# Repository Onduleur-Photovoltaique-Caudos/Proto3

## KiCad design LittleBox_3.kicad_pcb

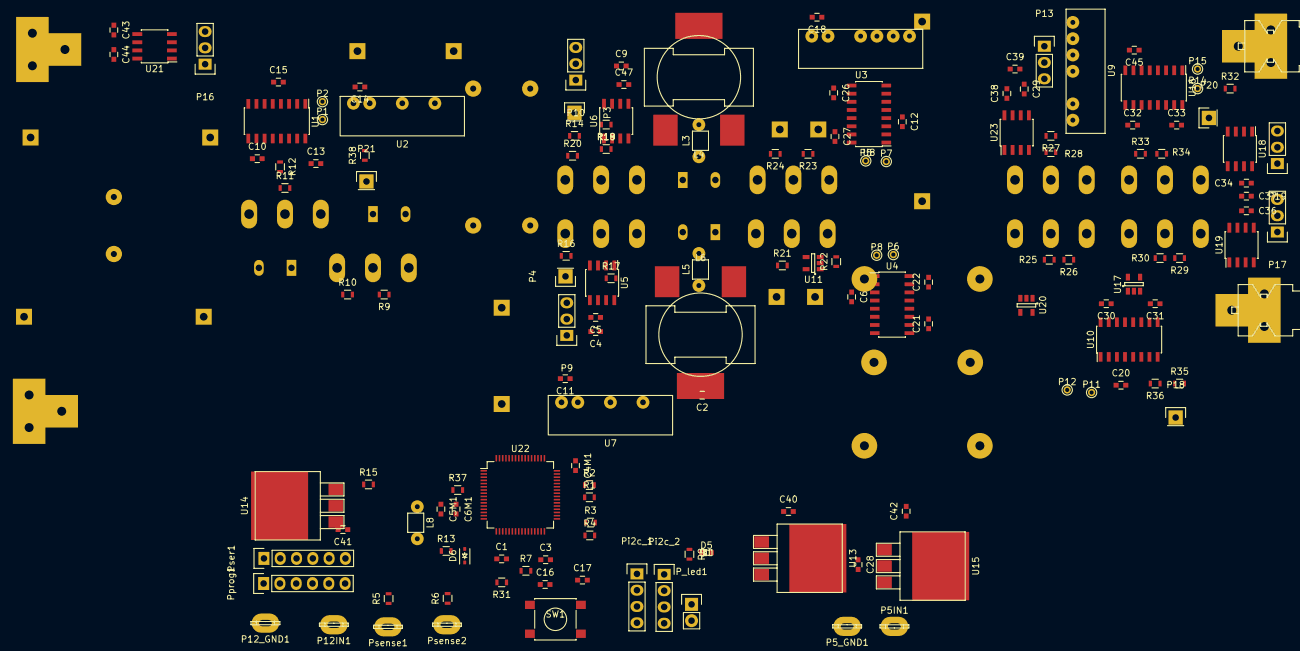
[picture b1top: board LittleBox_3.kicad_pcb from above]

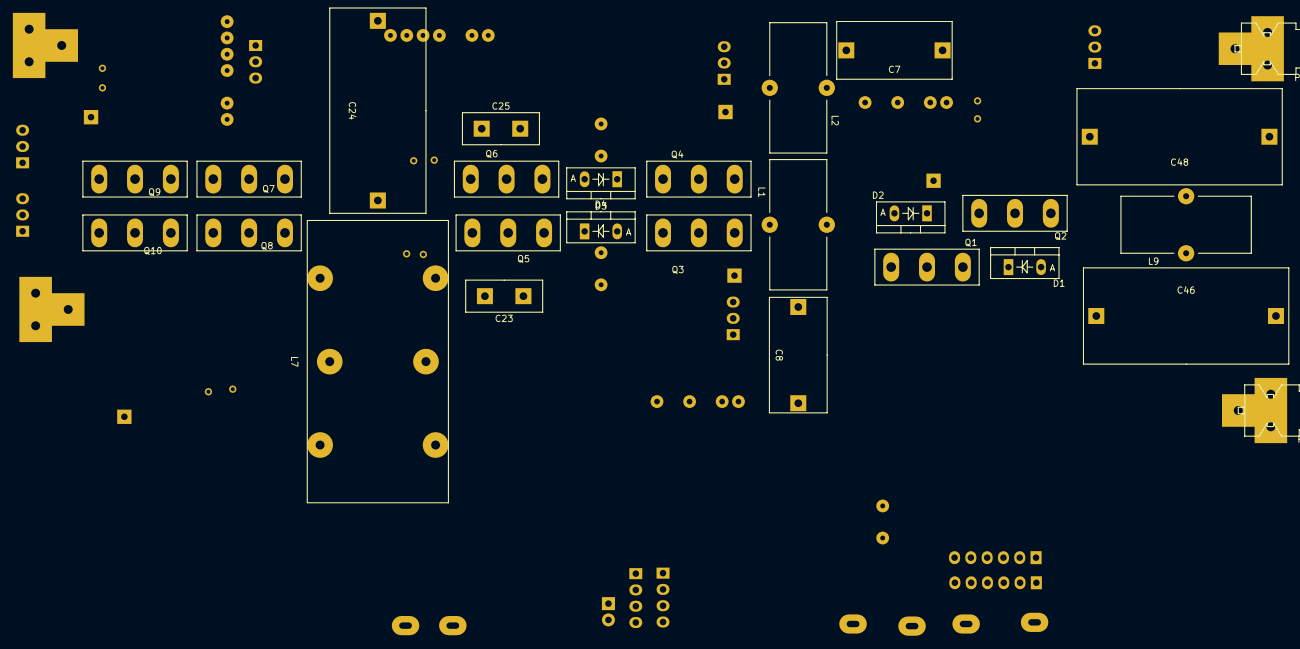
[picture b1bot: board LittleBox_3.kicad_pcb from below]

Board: 6 copper layers, 171 parts (27 on the bottom side), 109 nets, no tracks yet.

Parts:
C1, C2, C3, C4M1, C6, C12, C15, C17, C20, C34, C36, C37, C38, C39, C43, C44, C45: 100n; C_0603
C4, C5, C9, C47: 0.1u; C_0603
C5M1: 10n; C_0603
C6M1, C16, C28, C40, C41, C42: 1u; C_0603
C7, C8: 0.5u 250V; C_Rect_L18_W8_P15
C10, C11, C13, C14, C18, C21, C22, C26, C27, C29, C30, C31, C32, C33: 4.7u; C_0603
C23, C25: 1n 1000V; C_Rect_L12_W5_P6
C24, C46, C48: 2.2uF 630V; C_Rect_W15_L32_P27.5
D1, D2, D3, D4: C3D06060A; Diode_TO-220_Vertical
D5: LED; LED-0603
D6: SD1206S040S0R5; SOD-323
L1, L2: 470uH; 2100HT-471-V-RC
L3, L5: Bead; BEAD-5
L4, L6: 1uH; SER20xx-xxxL
L7: 1.2m; TOROID_15_44_22
L8: 2u; BEAD-5
L9: 330uH; 2100HT-471-V-RC
P1, P2, P5, P6, P7, P8, P11, P12, P14, P15: CONN_01X01; PINTST
P3, P4, P20: CONN_01X01; Socket_Strip_Straight_1x01
P5IN1, P5_GND1, P12IN1, P12_GND1: CONN_1; FASTON_110-1
P9, P10, P13, P16, P17, P19: CONN_01X03; Pin_Header_Straight_1x03
P18, P21: CONN_01X01; Pin_Header_Straight_1x01
P400IN+1, P400IN-1: CONN_1; FASTON250_Slanted30-1
POUT1, POUT2: CONN_1; FASTON250_Slanted30-1
P_led1: CONN_2; Pin_Header_Straight_1x02
Pi2c_1, Pi2c_2: CONN_4; Pin_Header_Straight_1x04
Pprog1: CONN_6; Pin_Header_Straight_1x06
Psense1, Psense2: CONN_1; FASTON_110-1
Pser1: CONN_6; Pin_Header_Straight_1x06
Q1, Q2, Q3, Q4, Q5, Q6: C3M0065090D; TO-247_Vertical_Neutral123
Q7, Q8, Q9, Q10: IPW6045CP; TO-247_Vertical_Neutral123
R1, R2, R3, R4: 0; R_0603
R5, R6, R7: 10k; R_0603
R8: 510; R_0603
R9, R11, R18, R19, R21, R23, R25, R28, R30, R34: 1k; R_0603
R10, R12, R17, R20, R22, R24, R26, R27, R29, R33: 1; R_0603
R13, R15, R31, R36, R37: 22K; R_0603
R14, R16, R32, R35, R38: 4.7M; R_0603
SW1: SW_PUSH; SW_SPST_PTS645
U1, U4, U8, U10, U16: ADUM3223; SOIC-16_3.9x9.9mm_Pitch1.27mm
U2, U7: B1212LS-1W
U3, U9: DY12D1212-2W
U5, U6, U18, U19, U21, U23: ACS712; SOIC-8_3.9x4.9mm_Pitch1.27mm
U11, U17, U20: IR25750; SOT-23-5
U13, U14: AZ1117-3.3; DPAK-3
U15: 7805; DPAK-3
U22: STM32F334R8T6; LQFP-64_10x10mm_Pitch0.5mm

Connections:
/B1: C23.1, C25.2, C26.1, L4.2, L6.1, L7.1, Q5.2, Q6.3, R23.1, U3.4, U8.9, U11.5
/H1_HON: P14.1, U16.2, U22.34
/H1_LON: P12.1, U10.1, U22.8
/H2_HON: P15.1, U16.1, U22.9
/H2_LON: P11.1, U10.2, U22.45
/M_I175: P10.2, R3.2, U6.7
/M_I225: P9.2, R1.2, U5.7
/M_IH1: U20.1, U22.24
/M_IH2: U17.1, U22.25
/M_IHFL: U11.1, U22.10
/M_IOUT1: P13.2, P19.2, R2.2, U18.7, U23.7
/M_IOUT2: P17.2, R4.2, U19.7
/M_VIN: P21.1, R37.1, R38.1
/ON225: P1.1, U1.2, U22.39
/PA1: P3.1, R13.2, R14.1, U22.15
/PA2: Pser1.3, U22.16
/PA3: Pser1.2, U22.17
/PA5: R8.1, U22.21
/PA6: P4.1, R15.2, R16.1, U22.22
/PA8: P7.1, U8.1, U22.41
/PA9: P8.1, U4.1, U22.42
/PA10: P6.1, U4.2, U22.43
/PA11: P5.1, U8.2, U22.44
/PA13: Pprog1.4, U22.46
/PA14: Pprog1.2, U22.49
/PB0: P20.1, R31.1, R32.1, U22.26
/PB1: P18.1, R35.2, R36.1, U22.27
/PB2: P16.2, U21.7, U22.28
/PB3: Pprog1.6, U22.55
/PB8: Pi2c_1.1, Pi2c_2.1, U22.61
/PB9: Pi2c_1.2, Pi2c_2.2, U22.62
/PB12: P2.1, U1.1, U22.33
/PB14: R3.1, R4.1, U22.35
/PB15: R1.1, R2.1, U22.36
/PC10: Pser1.5, U22.51
/inverter_microcontroller/BOO0: R7.1, U22.60
/inverter_microcontroller/NRST: C17.1, Pprog1.5, SW1.1, U22.7
/inverter_microcontroller/PD2: R5.1, U22.54
/inverter_microcontroller/VBAT: C16.1, U22.1
/inverter_microcontroller/VDD: C1.2, C2.2, C3.2, C4M1.1, D6.1, Pprog1.1, U22.19, U22.32, U22.48, U22.64
/inverter_microcontroller/VSS: C1.1, C2.1, C3.1, C4M1.2, Pprog1.3, U22.18, U22.31, U22.47, U22.63
DIS: U1.5, U4.5, U8.5, U10.5, U16.5, U22.6
GND_12: C11.1, C14.1, C18.1, C29.1, U2.2, U3.2, U7.2, U9.2
GND_A: C4.2, C5.2, C5M1.1, C6M1.1, C9.2, C34.1, C36.2, C37.2, C38.2, C39.2, C40.1, C43.1, C44.1, C47.2, P9.3, P10.3, P13.3, P16.3, P17.3, P19.3, R13.1, R15.1, R31.2, R36.2, R37.2, U5.5, U6.5, U13.1, U18.5, U19.5, U21.5, U22.12, U23.5
GND_P: C6.2, C7.2, C8.2, C10.1, C12.1, C15.2, C16.2, C17.2, C20.2, C22.1, C23.2, C24.2, C28.1, C30.1, C31.1, C41.1, C42.1, C46.1, C48.1, D2.1, D5.2, P5_GND1.1, P12_GND1.1, P400IN-1.1, P_led1.1, Pi2c_1.4, Pi2c_2.4, Pser1.4, Q1.3, Q5.3, Q8.3, Q10.3, R6.2, R7.2, R9.2, R21.1, R25.1, R30.1, SW1.2, U1.4, U1.9, U4.4, U4.14, U8.4, U10.4, U10.9, U10.14, U11.4, U14.1, U15.1, U17.4, U20.4
unnamed: C5.1, U5.6
unnamed: C5M1.2, C6M1.2, D6.2, L8.2, U22.13
unnamed: C7.1, L1.2, R16.2, U5.1, U5.2
unnamed: C8.1, L2.1, R14.2, U6.1, U6.2
unnamed: C13.1, D2.2, L2.2, Q2.3, R11.2, U1.14, U2.6
unnamed: C13.2, U1.16, U2.4
unnamed: C21.1, D3.2, Q3.3, R18.1, U4.9, U7.4
unnamed: C21.2, U4.11, U7.6
unnamed: C24.1, L7.2, U23.1, U23.2
unnamed: C26.2, U3.5, U8.11
unnamed: C27.2, U8.16
unnamed: C32.1, Q7.3, Q8.2, R28.1, U9.4, U16.9, U19.1, U19.2, U20.5
unnamed: C32.2, U9.5, U16.11
unnamed: C33.1, Q9.3, Q10.2, R34.1, U9.6, U16.14, U17.5, U18.3, U18.4
unnamed: C34.2, U18.6
unnamed: C36.1, U19.6
unnamed: C38.1, U23.6
unnamed: C43.2, U21.6
unnamed: C45.1, U16.4
unnamed: C47.1, U6.6
unnamed: C48.2, L9.1, U21.1, U21.2
unnamed: D1.1, L1.1, Q1.2
unnamed: D3.1, L5.1
unnamed: D4.1, Q4.2
unnamed: D4.2, L3.1
unnamed: D5.1, P_led1.2, R8.2
unnamed: L3.2, L4.1
unnamed: L5.2, L6.2
unnamed: P400IN+1.1, U21.3, U21.4
unnamed: POUT1.1, R32.2, U18.1, U18.2
unnamed: POUT2.1, R35.1, U19.3, U19.4
unnamed: Psense1.1, R5.2
unnamed: Psense2.1, R6.1
unnamed: Q1.1, R9.1, R10.2
unnamed: Q2.1, R11.1, R12.2
unnamed: Q3.1, R17.2, R18.2
unnamed: Q4.1, R19.1, R20.1
unnamed: Q5.1, R21.2, R22.2, U11.3
unnamed: Q6.1, R23.2, R24.2
unnamed: Q7.1, R27.2, R28.2
unnamed: Q7.2, Q9.2, U23.3, U23.4
unnamed: Q8.1, R25.2, R26.2, U20.3
unnamed: Q9.1, R33.2, R34.2
unnamed: Q10.1, R29.2, R30.2, U17.3
unnamed: R10.1, U1.10
unnamed: R12.1, U1.15
unnamed: R17.1, U4.10
unnamed: R20.2, U8.15
unnamed: R22.1, U4.15
unnamed: R24.1, U8.10
unnamed: R26.1, U10.15
unnamed: R27.1, U16.10
unnamed: R29.1, U10.10
unnamed: R33.1, U16.15
unnamed: U9.7, U16.16
V175: C27.1, Q4.3, R19.2, U3.6, U6.3, U6.4, U8.14
V225: Q3.2, U5.3, U5.4
V400+: C25.1, C46.2, D1.2, L9.2, Q2.2, Q6.2, R38.2
VCC3_A: C4.1, C9.1, C37.1, C39.1, C44.2, P9.1, P10.1, P13.1, P16.1, P17.1, P19.1, U5.8, U6.8, U18.8, U19.8, U21.8, U23.8
VCC5: C42.2, U13.3, U14.3, U15.2
VCC5_IN: C28.2, P5IN1.1, U15.3
VCC12: C10.2, C11.2, C14.2, C18.2, C22.2, C29.2, C30.2, C31.2, P12IN1.1, U1.11, U2.1, U3.1, U4.16, U7.1, U9.1, U10.11, U10.16
VDD3_A: C40.2, L8.1, U13.2
VDD3_D: C6.1, C12.2, C15.1, C20.1, C41.2, C45.2, Pi2c_1.3, Pi2c_2.3, Pser1.1, U1.3, U1.8, U4.3, U4.8, U8.3, U8.8, U10.3, U10.8, U14.2, U16.3, U16.8

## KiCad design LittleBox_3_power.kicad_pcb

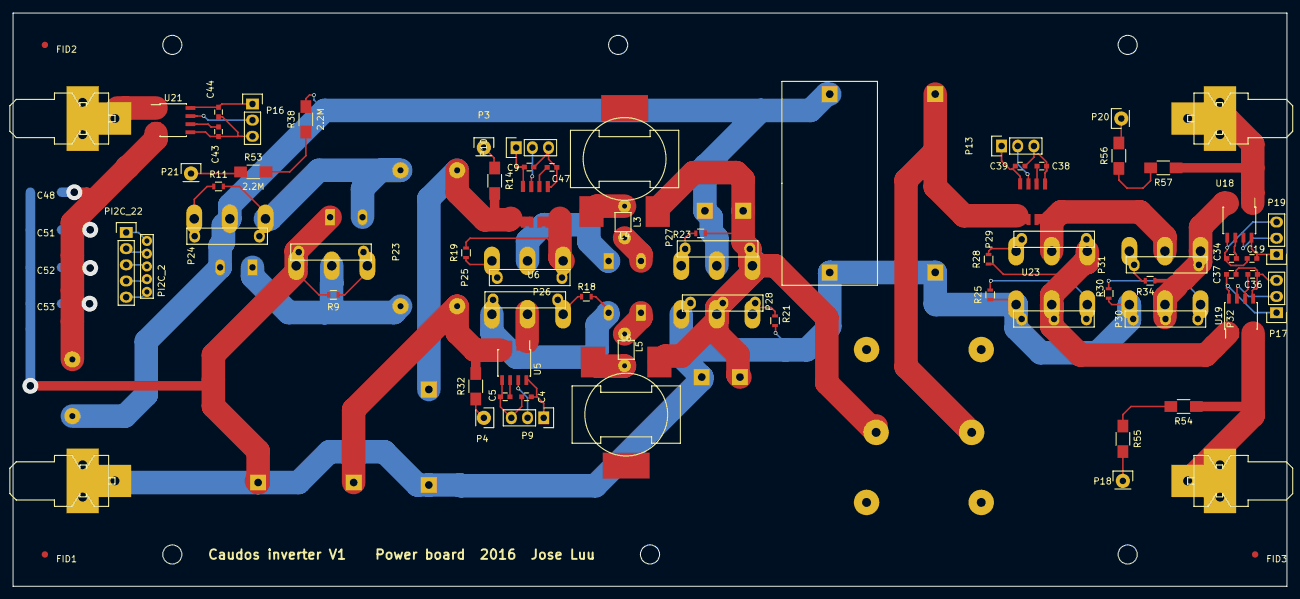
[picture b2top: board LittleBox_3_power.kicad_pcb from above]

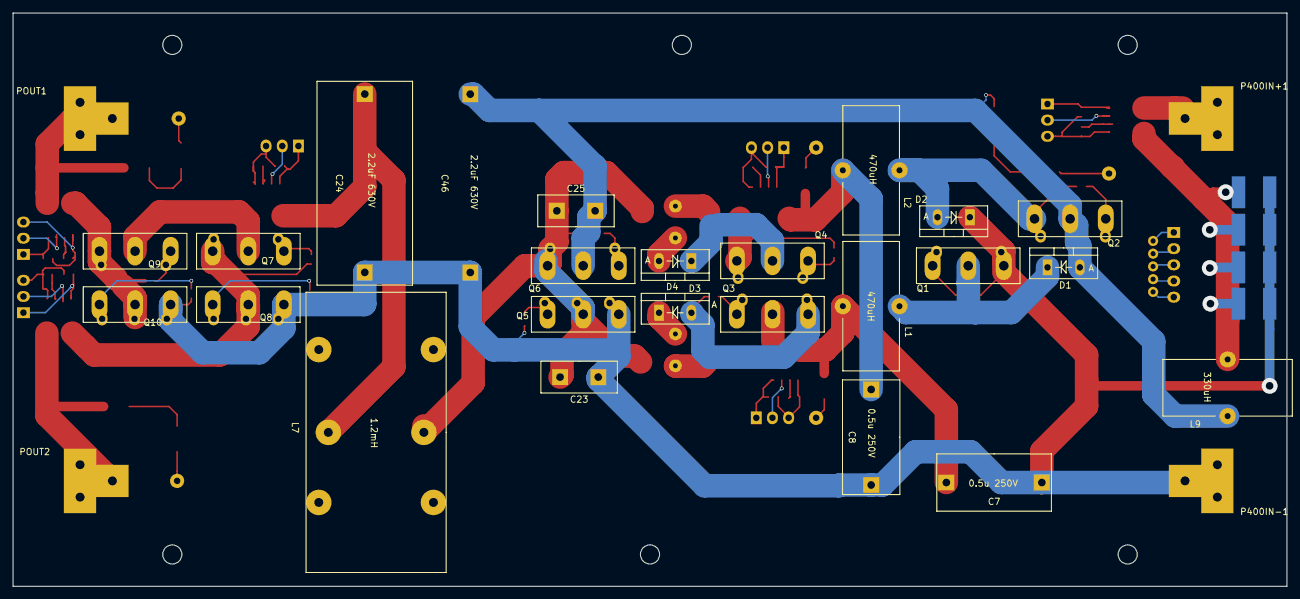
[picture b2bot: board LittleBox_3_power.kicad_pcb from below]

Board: 2 copper layers, 200.0 x 90.0 mm, 98 parts (23 on the bottom side), 60 nets.

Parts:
C4, C5, C9, C19, C34, C36, C37, C38, C39, C43, C44, C47: 100n; C_0603
C7, C8: 0.5u 250V; C_Rect_L18_W8_P15
C23, C25: 1n 1000V; C_Rect_L12_W5_P6
C24, C46: 2.2uF 630V; C_Rect_W15_L32_P27.5
C48: 2.2uF 630V; MLCC_SuperCap_5750_BackCu
C51, C52, C53: 1uF 630V; MLCC_SuperCap_5750_BackCu
D1, D2, D3, D4: C3D06060A; Diode_TO-220_Vertical
FID1, FID2, FID3: Fiducial_1mm_Dia_2.54mm_Outer_CopperTop
L1, L2: 470uH; 2100HT-471-V-RC
L3, L5: Bead; BEAD-5
L4, L6: 1uH; SER20xx-xxxL
L7: 1.2mH; TOROID_15_44_22
L9: 330uH; 2100HT-471-V-RC
P3: CONN_01X01; Pin_Header_Straight_1x01_round
P4, P20: CONN_01X01; Socket_Strip_Straight_1x01
P9, P10, P13, P16, P17, P19: CONN_01X03; Pin_Header_Straight_1x03
P18, P21: CONN_01X01; Pin_Header_Straight_1x01
P23, P24, P25, P26, P27, P29, P31: CONN_01X02; Pin_Header_Straight_1x02_round
P28, P30, P32: CONN_01X03; Pin_Header_Straight_1x03_round
P400IN+1, P400IN-1: CONN_1; FASTON250_Slanted30-1
PI2C_2: CONN_01X05; Header_1x5_metric
PI2C_22: CONN_01X05; Pin_Header_Straight_1x05
POUT1, POUT2: CONN_1; FASTON250_Slanted30-1
Q1, Q2, Q3, Q4, Q5, Q6: C3M0065090D; TO-247_Vertical_Neutral123
Q7, Q8, Q9, Q10: IPW6045CP; TO-247_Vertical_Neutral123
R9, R11, R18, R19, R21, R23, R25, R28, R30, R34: 1k; R_0603
R14, R32, R38, R53, R54, R55, R56, R57: 2.2M; R_1206_HandSoldering
U5, U18, U19, U21: ACS712; SOIC-8_3.9x4.9mm_Pitch1.27mm
U6, U23: ACS712

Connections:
/B1: C23.1, C25.2, L4.2, L6.1, L7.1, P27.2, P28.2, Q5.2, Q6.3, R23.1
/M_VIN: P21.1, R53.1
/PA1: P3.1, R14.1
/PA6: P4.1, R32.1
/PB0: P20.1, R56.2
/PB1: P18.1, R55.2
/PB7: PI2C_2.1, PI2C_22.1
/PB8: PI2C_2.2, PI2C_22.2
/PB9: PI2C_2.3, PI2C_22.3
GND_12: C7.2, C8.2, C23.2, C24.2, C46.1, C48.1, C51.1, C52.1, C53.1, D2.1, P23.2, P28.3, P30.3, P32.3, P400IN-1.1, Q1.3, Q5.3, Q8.3, Q10.3, R9.2, R21.1, R25.1, R30.1
GND_A: C4.2, C5.2, C9.2, C19.1, C34.1, C36.2, C37.2, C38.2, C39.2, C43.1, C44.1, C47.2, P9.3, P10.3, P13.3, P16.3, P17.3, P19.3, U5.5, U6.5, U18.5, U19.5, U21.5, U23.5
GND_D: PI2C_2.5, PI2C_22.5
unnamed: C5.1, U5.6
unnamed: C7.1, L1.2, R32.2, U5.3, U5.4
unnamed: C8.1, L2.1, R14.2, U6.1, U6.2
unnamed: D2.2, L2.2, P24.2, Q2.3, R11.2
unnamed: D3.2, P26.2, Q3.3, R18.1
unnamed: C24.1, L7.2, U23.1, U23.2
unnamed: P29.2, P30.2, Q7.3, Q8.2, R28.1, U19.1, U19.2
unnamed: P31.2, P32.2, Q9.3, Q10.2, R34.1, U18.3, U18.4
unnamed: C34.2, U18.6
unnamed: C36.1, U19.6
unnamed: C38.1, U23.6
unnamed: C43.2, U21.6
unnamed: C47.1, U6.6
unnamed: C48.2, C51.2, C52.2, C53.2, L9.1, U21.3, U21.4
unnamed: D1.1, L1.1, Q1.2
unnamed: D3.1, L5.1
unnamed: D4.1, Q4.2
unnamed: D4.2, L3.1
unnamed: L3.2, L4.1
unnamed: L5.2, L6.2
unnamed: P9.2, U5.7
unnamed: P10.2, U6.7
unnamed: P13.2, U23.7
unnamed: P16.2, U21.7
unnamed: P17.2, U19.7
unnamed: P19.2, U18.7
unnamed: P23.1, Q1.1, R9.1
unnamed: P24.1, Q2.1, R11.1
unnamed: P25.1, Q4.1, R19.1
unnamed: P26.1, Q3.1, R18.2
unnamed: P27.1, Q6.1, R23.2
unnamed: P28.1, Q5.1, R21.2
unnamed: P29.1, Q7.1, R28.2
unnamed: P30.1, Q8.1, R25.2
unnamed: P31.1, Q9.1, R34.2
unnamed: P32.1, Q10.1, R30.2
unnamed: P400IN+1.1, U21.1, U21.2
unnamed: POUT1.1, R57.1, U18.1, U18.2
unnamed: POUT2.1, R54.1, U19.3, U19.4
unnamed: Q7.2, Q9.2, U23.3, U23.4
unnamed: R38.1, R53.2
unnamed: R54.2, R55.1
unnamed: R56.1, R57.2
V175: P25.2, Q4.3, R19.2, U6.3, U6.4
V225: Q3.2, U5.1, U5.2
V400+: C25.1, C46.2, D1.2, L9.2, Q2.2, Q6.2, R38.2
VCC5_A: C4.1, C9.1, C19.2, C37.1, C39.1, C44.2, P9.1, P10.1, P13.1, P16.1, P17.1, P19.1, U5.8, U6.8, U18.8, U19.8, U21.8, U23.8
VDD3_D: PI2C_2.4, PI2C_22.4

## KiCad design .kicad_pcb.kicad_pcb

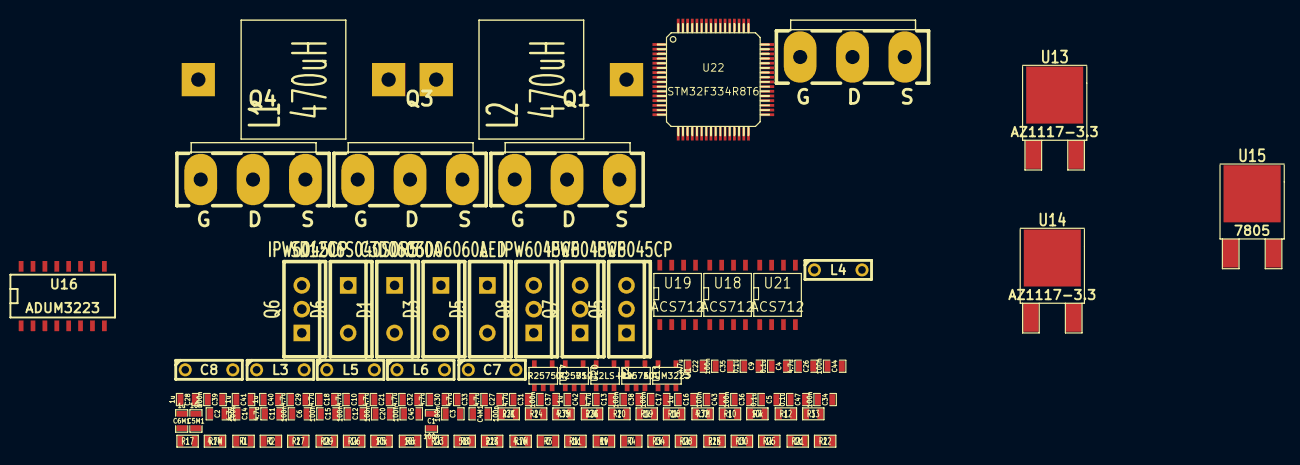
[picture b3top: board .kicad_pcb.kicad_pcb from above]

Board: 2 copper layers, 112 parts (0 on the bottom side), 70 nets, no tracks yet.

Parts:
C1, C2, C3, C4M1, C6, C12, C15, C17, C20, C34, C35, C36, C37, C38, C39, C43, C44, C45: 100n; SM0603_Capa
C4, C5, C9, C47: 0.1u; SM0603_Capa
C5M1: 10n; SM0603_Capa
C6M1, C16, C28, C40, C41, C42: 1u; SM0603_Capa
C7, C8: 0.5u 250V; C2
C10, C11, C13, C14, C18, C21, C22, C26, C27, C29, C30, C31, C32, C33: 4.7u; SM0603_Capa
D1, D3: C3D06060A; TO220_VERT_2
D5: LED; TO220_VERT_2
D6: SD1206S040S0R5; TO220_VERT_2
L1, L2: 470uH; L-toroid-8X4
L3, L5: Bead; C2
L4, L6: 1uH; C2
Q1, Q2, Q3, Q4: C3M0065090D; TO-247_Vertical_FET-GDS_largePads
Q5, Q6, Q7, Q8: IPW6045CP; TO220_VERT_GDS
R1, R2, R3, R4: 0; SM0603
R5, R6, R7: 10k; SM0603
R8: 510; SM0603
R9, R11, R18, R19, R21, R23, R25, R26, R28, R29, R30, R34: 1k; SM0603
R10, R12, R17, R20, R22, R24, R27, R33: 1; SM0603
R13, R15, R31, R36: 22K; SM0603
R14, R16, R32, R35: 4.7M; SM0603
U1: ADUM3223; SOT23-5
U2: B1212LS-1W; SOT23-5
U11, U17, U20: IR25750; SOT23-5
U13, U14: AZ1117-3.3; DPAK2
U15: 7805; DPAK2
U16: ADUM3223; SO16N
U18, U19, U21: ACS712; SO8N
U22: STM32F334R8T6; AB2_LQFP64

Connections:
/B1: C26.1, L4.2, L6.2, R23.1, U11.5
/H2_HON: U16.2, U22.9
/H2_LON: U16.1, U22.45
/M_IH1: U20.1, U22.24
/M_IHFL: U11.1, U22.10
/M_IOUT1: R2.2, U18.7
/M_IOUT2: R4.2, U19.7
/ON225: U1.2, U22.39
/PA1: R13.2, R14.1, U22.15
/PA5: R8.1, U22.21
/PA6: R15.2, R16.1, U22.22
/PB0: R31.1, R32.1, U22.26
/PB1: R35.1, R36.1, U22.27
/PB2: U21.7, U22.28
/PB12: U1.1, U22.33
/PB14: R3.1, R4.1, U22.35
/PB15: R1.1, R2.1, U22.36
/inverter_microcontroller/BOO0: R7.1, U22.60
/inverter_microcontroller/NRST: C17.1, U22.7
/inverter_microcontroller/PD2: R5.1, U22.54
/inverter_microcontroller/VBAT: C16.1, U22.1
/inverter_microcontroller/VDD: C1.2, C2.2, C3.2, C4M1.1, D6.1, U22.19, U22.32, U22.48, U22.64
/inverter_microcontroller/VSS: C1.1, C2.1, C3.1, C4M1.2, U22.18, U22.31, U22.47, U22.63
DIS: U1.5, U16.5, U22.6
GNDA: C43.1, C44.1, R31.2, R36.2, U21.5
GND_12: C11.1, C14.1, C18.1, U2.2
GND_A: C4.2, C5.2, C5M1.1, C6M1.1, C9.2, C34.2, C35.2, C36.2, C37.2, C38.2, C39.2, C40.1, C47.2, R13.1, R15.1, U18.5, U19.5, U22.12
GND_D: C6.2, C15.2, C16.2, C17.2, C20.2, C28.1, C41.1, C42.1, C45.1, D5.2, R6.2, R7.2, U1.4, U16.4
GND_P: C7.2, C8.2, C10.1, Q1.3, R9.2, R25.1, R30.1, U11.4, U16.14, U17.4, U20.4
unnamed: Q1.2, R9.1, R10.2
unnamed: R33.1, U16.10
unnamed: R29.1, U16.15
unnamed: Q2.2, R11.1, R12.2
unnamed: C36.1, U19.6
unnamed: C43.2, U21.6
unnamed: D1.1, L1.1, Q1.1
unnamed: R22.2, U11.3
unnamed: R23.2, R24.2
unnamed: Q3.2, R17.2, R18.2
unnamed: D3.1, L5.1
unnamed: R25.2, R26.2, U20.3
unnamed: R29.2, R30.2, U17.3
unnamed: Q4.2, R19.2, R20.1
unnamed: C21.1, D3.2, Q3.3, R18.1
unnamed: L5.2, L6.1
unnamed: L3.2, L4.1
unnamed: C22.2, R20.2
unnamed: C13.2, U2.4
unnamed: C34.1, U18.6
unnamed: C32.2, U16.11
unnamed: D5.1, R8.2
unnamed: C13.1, L2.2, Q2.3, R11.2
unnamed: R33.2, R34.2
unnamed: R27.2, R28.2
unnamed: R28.1, U19.1, U19.2, U20.5
unnamed: C8.1, L2.1, R14.2
unnamed: R35.2, U19.3, U19.4
unnamed: L1.2, R16.2
unnamed: U21.3, U21.4
unnamed: R32.2, U18.3, U18.4
unnamed: C32.1, R34.1, U16.9, U17.5, U18.1, U18.2
unnamed: C5M1.2, C6M1.2, D6.2, U22.13
V175: C22.1, Q4.3, R19.1
V400+: D1.2, Q2.1, U21.1, U21.2
VCC3_A: C4.1, C9.1, C35.1, C37.1, C39.1, U18.8, U19.8
VCC5: U13.3, U14.3
VCC5A: C44.2, U21.8
VCC12: C10.2, C11.2, C14.2, C27.2, C31.2, C33.2, U2.1, U16.16
VDD3_A: C40.2, U13.2
VDD3_D: C6.1, C12.2, C15.1, C45.2, U1.3, U14.2, U16.3, U16.8

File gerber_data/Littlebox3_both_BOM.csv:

Component,Comment,Designator,Footprint,Pins,Quantity total
1972,470pF,C35 C50,C_0603,2,2
4597,2.2K,R39 R42 R43 R45 R48 R49,R_0603,2,6
15331,100n,C1 C2 C3 C4 C4M1 C5 C6 C9 C12 C15 C17 C19 C20 C34 C36 C37 C38 C39 C43 C44 C45 C47,C_0603,2,22
16531,1u,C6M1 C16 C28 C40 C41 C42 C49,C_0603,2,7
20375,4.7u,C10 C11,C_0805,2,2
20375,4.7u,C13 C14 C18 C21 C22 C26 C27 C29 C30 C31 C32 C33,C_0603,2,12
21903,0R,R1 R2 R3 R4 R51 R52,R_0603,2,6
21904,1k,R9 R11 R18 R19 R21 R23 R25 R28 R30 R34,R_0603,2,10
23663,1R,R10 R12 R17 R20 R22 R24 R26 R27 R29 R33,R_0603,2,10
23920,510R,R8,R_0603,2,1
23939,6.8K,R40 R41 R44 R46 R47 R50,R_0603,2,6
26547,10k,R5 R6 R7,R_0603,2,3
32812,22K,R13 R15 R31 R36 R37,R_0603,2,5
58143,10n,C5M1,C_0603,2,1

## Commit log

2015-07-19 Finished most of the schematics, missing fan control
2015-07-26 Layout stabilisé
2015-07-27 couche "power" stabilisee
2016-04-08 Last mods
2016-09-10 Check high voltage spacings and modify accordingly
2016-11-10 gerber generation
2016-11-11 Ajout references elecrow Ajout parametrage KiBOM generateur de BOM en python
2016-11-11 Deplacement des fiducial et du point de reference afin d'avoir des coordonees positives
2016-11-11 Deplacement des fiducials et de l'origine afin d'avoir des coordonees positives
2016-11-11 Correction masque incorrect sur C53 Ajout texte Suppression de git de fichiers inutiles
2016-11-11 Ajout texte
2016-11-12 Titre schema principal References Elecrow pour board power Changement origine pour board data (coin en bas a gauche)
2016-11-12 Indications dans Cmts.User
2017-01-22 First PCB order
